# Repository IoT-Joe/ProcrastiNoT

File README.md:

# ProcrastiNoT 
--------
![Pasted image 20261012040526.png]]

ProcrastiNoT is a RaspberryPi Operated project : basically a 2 part system, Table Deck and watch, aimed at helping high school students managing thier time efficiently.
## What it is
------

ProcarstiNoT is simply a two devices ,Table Dock and Custom Watch, built system to monitor the Student Performance Across the day through tracking the following : 
1. The Student Presence Time on Studying Table
2. The Actual Tabs opened on Laptop {Closing Prohibited Tabs on Studying Times}
3. The Student Actual Focus Time {Through DL Model that count actual time where student were focusing on Laptop}
and Keep Student Aware using the Custom Watch When he bypass Breaks Time, With sensible punishment through Vibration motor to force student returning to his studying place.
## Why?
-------

The project is actually created to satisfy as a solution to two main problems :
1. High School Students That lose a lot of untrack times through Procrastination and Long Breaks
2. Parents Needs to monitor their children Performance and actual studying time daily

## Project status
----

The PCB design, renders, and an Arduino starter firmware are included here.

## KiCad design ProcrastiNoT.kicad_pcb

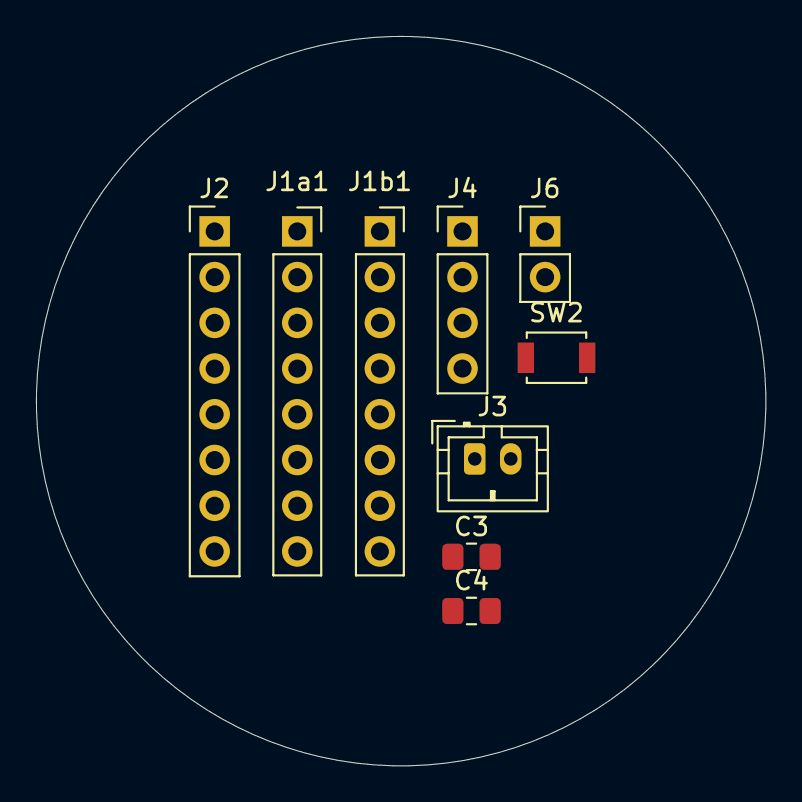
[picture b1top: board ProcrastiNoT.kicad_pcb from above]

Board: 2 copper layers, 40.5 x 40.5 mm, 9 parts (0 on the bottom side), 10 nets, no tracks yet.

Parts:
C3: 100nF; C_0805_2012Metric_Pad1.18x1.45mm_HandSolder
C4: 100uF; C_0805_2012Metric_Pad1.18x1.45mm_HandSolder
J1a1, J1b1: Conn_01x08_Pin; PinSocket_1x08_P2.54mm_Vertical
J2: Conn_01x08_Pin; PinHeader_1x08_P2.54mm_Vertical
J3: Conn_01x02_Pin; JST_PH_B2B-PH-K_1x02_P2.00mm_Vertical
J4: Conn_01x04_Pin; PinHeader_1x04_P2.54mm_Vertical
J6: Conn_01x02_Pin; PinHeader_1x02_P2.54mm_Vertical
SW2: SW_Omron_B3FS; SW_SPST_B3U-1000P

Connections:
+3V3: C3.1, J1b1.3, J2.7, J3.1, J4.2
/BAT-: J3.2, J4.3
/CS: J1a1.3, J2.2
/DC: J1a1.1, J2.3
/GPIO0: J1b1.8, SW2.2
/GPIO4: J1b1.4, J2.6
/RES: J1a1.6, J2.4
/SDA: J1a1.2, J2.5
/VSW+: C4.1, J6.1
GND: C3.2, C4.2, J1b1.2, J2.8, J4.4, SW2.1
